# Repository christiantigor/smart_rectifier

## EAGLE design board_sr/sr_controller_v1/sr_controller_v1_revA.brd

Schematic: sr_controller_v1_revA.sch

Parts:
BAT1: BATTERY20PTH; BATTCOM_20MM_PTH
BUC_SPLY: AK300/2
C1, C9: C4.7uF; C0805
C3, C5, C14: C100N; C0805K
C4, C6: C1N; C0805K
C7, C8: C100uF; 153CLV-0605
C10, C12: C100nF; C0805
C11, C13: C22pF; C0805
D1: 1N4007; DO214AA
D3: TVSARRAY_5LANE; SOT363
DUMMY_A: AK500/2
DUMMY_B: AK500/2
DUMMY_C: AK500/2
F1, F5: 4A; FUSE1
F3: 10A; FUSE1
F4: 7A; FUSE1
FAN_A: 1X2-3.5MM
FAN_B: 1X2-3.5MM
FROM_LTC_REG: AK300/3
IC1: GSM_SIM900_LITERAL; SIM900_SMT
IC2: 74HC595D; SO16
INDICATOR_CONN: MA08-2
J1: SIMHOLDERSIM; SIMHOLDER
J2, J3, J4, J5, J6, J7, J8, J9: WIRE_HOLE-14AWG
K1: G5L; G5LE
LED1, LED2: LEDCHIPLED_0805; CHIPLED_0805
MDM_REG_A: AK300/2
MDM_REG_B: AK300/2
MDM_SPLY_HT_X1_X3: AK300/5
MDM_SPLY_HX_A: AK500/2
MDM_SPLY_HX_B: AK500/2
PCB1: RASPBERRY_PI_B+_NO_MOUNT; RASPBERRY_PI_B+
Q1: 32kHz; TC38H
R1, R2, R4, R7, R10, R12, R14, R15, R16, R22, R25, R28, R37, R38, R39, R40, R41, R42, R43, R44, R45, R46, R47, R48, R49, R50, R51: R10K; R0805
R3, R31, R34: R2K; R0805
R5, R6, R11, R13, R21, R24, R30, R35, R36: R1K; R0805
R8, R23, R26: R220R; R0805
R17, R29: R5.1K; R0805
R18, R19, R20: R22R; R0805
R27: R120R; R0805
R32: R270K; 0309/10
R33: R5.1K; 0309/10
SCADA_REG_A: AK300/2
SCADA_REG_B: AK300/2
SCADA_SPLY: AK500/2
SCPC_SPLY: AK300/2
SJ1, SJ2: SOLDERJUMPER; SOLDERJUMPER_ARROW_NOPASTE
SJ3: SOLDERJUMPERCLOSED; SOLDERJUMPER_CLOSEDWIRE
T1, T2, T3, T4: MMBT2222ALT1-NPN-SOT23-BEC; SOT23-BEC
TO_LTC_REG: AK300/2
U1: RTC_DS1307; SOIC8_150MIL
U3: RHT03_DHT-22_AM2302; RHT03_DHT-22
U$1: ARDUINO_PRO_MINI
U$2, U$4: ACS712; SO08
U$3, U$6: DCDCMODULE
U$5: FB0603; L0603
U$8: 74HC4053D; SO16
U$9: TRANSFORMER; TV16
VAC: AK300/2
V_ACCU: AK300/2
V_PWR_SPLY: AK300/2
X1: SMACONNECTOR; SMA90_DIP

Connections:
+3V3: R23.1, R26.1, R37.1, R38.1, R44.1, SJ2.2, U$5.2
+5V: C1.2, C3.2, C5.2, IC2.16 (VCC), INDICATOR_CONN.15, PCB1.2 (5V0), PCB1.4 (5V0), R1.1, R39.1, R40.1, R41.1, R42.1, R43.1, R45.1, R46.1, R47.1, R48.1, R49.1, R50.1, R51.1, SJ1.2, U1.8 (VCC), U3.VDD, U$1.21 (VCC), U$2.8 (VCC), U$4.8 (VCC), U$8.16 (VCC)
+6.5V: FROM_LTC_REG.3, MDM_SPLY_HX_A.1, R14.1
+13.5V: FROM_LTC_REG.1, MDM_SPLY_HT_X1_X3.4, R28.1
+19.5V: FROM_LTC_REG.2, MDM_SPLY_HX_A.2, R2.1
AGND: C3.1, C4.1, C5.1, C6.1, C14.1, SJ3.2, U$2.5 (GND), U$4.5 (GND)
ARDU_FLASH: INDICATOR_CONN.4, R45.2, U$1.14 (*11)
ARDU_RX: PCB1.26 (!CE!/GPIO7), U$1.2 (RXI)
ARDU_TX: PCB1.24 (!CE0!/GPIO8), R30.2, R31.1
CTRL_CHARGING: PCB1.40 (GPIO21), R6.1
CTRL_LED0: IC2.15 (QA), INDICATOR_CONN.13, R43.2
CTRL_LED1: IC2.1 (QB), INDICATOR_CONN.14, R51.2
CTRL_LED2: IC2.2 (QC), INDICATOR_CONN.11, R42.2
CTRL_LED3: IC2.3 (QD), INDICATOR_CONN.12, R50.2
CTRL_LED4: IC2.4 (QE), INDICATOR_CONN.9, R41.2
CTRL_LED5: IC2.5 (QF), INDICATOR_CONN.10, R49.2
CTRL_LED6: IC2.6 (QG), INDICATOR_CONN.7, R40.2
CTRL_LED7: IC2.7 (QH), INDICATOR_CONN.8, R48.2
CTRL_LED8: INDICATOR_CONN.5, R39.2, U$1.15 (12)
CTRL_LED9: INDICATOR_CONN.6, R46.2, U$1.16 (13)
CTRL_SIM_PWRKEY: PCB1.12 (GPIO18), R27.1
DHT_DATA: R1.2, U3.DATA, U$1.13 (*10)
GND: BAT1.2 (-), BUC_SPLY.2, C1.1, C7.-, C8.-, C9.1, C10.1, C11.1, C12.1, C13.1, D3.2 (A), FAN_A.1, FAN_B.1, IC1.P$17 (GND), IC1.P$18 (GND), IC1.P$29 (GND), IC1.P$39 (GND), IC1.P$45 (GND), IC1.P$46 (GND), IC1.P$53 (GND), IC1.P$54 (GND), IC1.P$58 (GND), IC1.P$59 (GND), IC1.P$61 (GND), IC1.P$62 (GND), IC1.P$63 (GND), IC1.P$64 (GND), IC1.P$65 (GND), IC2.8 (GND), IC2.13 (G), INDICATOR_CONN.16, J1.C5 (GND), MDM_REG_A.2, MDM_REG_B.1, MDM_SPLY_HT_X1_X3.2, MDM_SPLY_HX_B.1, PCB1.9 (GND), PCB1.25 (GND), PCB1.39 (GND), R3.2, R8.2, R11.2, R13.2, R15.2, R17.2, R22.1, R25.1, R29.2, R31.2, R34.2, SCADA_REG_A.2, SCADA_REG_B.1, SCADA_SPLY.2, SCPC_SPLY.2, SJ3.1, T1.E, T2.E, T3.E, T4.E, TO_LTC_REG.2, U1.4 (GND), U3.GND, U$1.4 (GND), U$1.23 (GND), U$3.GND#0 (GNDI), U$3.GND#1 (GNDO), U$6.GND#0 (GNDI), U$6.GND#1 (GNDO), U$8.6 (/E), U$8.7 (VEE), U$8.8 (GND), V_ACCU.1, V_PWR_SPLY.1, X1.GND1, X1.GND2, X1.GND3, X1.GND4
GPIO11: IC1.P$67 (GPIO11)
GPIO12: IC1.P$68 (GPIO12)
MDM_INDC_0: MDM_SPLY_HX_B.2, PCB1.38 (GPIO20), R5.2
MDM_INDC_1: MDM_SPLY_HT_X1_X3.1, PCB1.32 (GPIO12), R35.2
MDM_INDC_2: MDM_SPLY_HT_X1_X3.3, PCB1.36 (GPIO16), R36.2
unnamed: R32.1, VAC.2
unnamed: U$9.IB, VAC.1
unnamed: Q1.1, U1.1 (X1)
unnamed: Q1.2, U1.2 (X2)
unnamed: BAT1.1 (+), U1.3 (VBAT)
unnamed: U$8.13 (1Y1), U$8.15 (2Z)
unnamed: U$8.4 (3Z), U$8.12 (1Y0)
unnamed: SJ1.1, U$3.VOUT
unnamed: SJ2.1, U$6.VOUT
unnamed: C4.2, U$2.6 (FILT)
unnamed: R6.2, T4.B
unnamed: C6.2, U$4.6 (FILT)
unnamed: F1.1A, MDM_REG_B.2
unnamed: F3.1A, SCADA_REG_B.2
unnamed: IC1.P$60 (RF_ANT), X1.ANTENNA (ANT)
unnamed: C7.+, C8.+, IC1.P$55 (VBAT1), IC1.P$56 (VBAT2), IC1.P$57 (VBAT3), U$5.1
unnamed: C9.2, IC1.P$26 (VRTC)
unnamed: IC1.P$33 (SIM_RST), R18.1
unnamed: IC1.P$32 (SIM_CLK), R19.1
unnamed: IC1.P$31 (SIM_DATA), R20.1
unnamed: LED1.C, T1.C
unnamed: LED1.A, R23.2
unnamed: LED2.C, T2.C
unnamed: R21.2, R22.2, T1.B
unnamed: LED2.A, R26.2
unnamed: R24.2, R25.2, T2.B
unnamed: R27.2, T3.B
unnamed: D1.A, K1.2, T4.C
unnamed: R30.1, U$1.1 (TXO)
unnamed: R32.2, U$9.IA
unnamed: C14.2, R33.1, U$9.OB
RPI_3V3: PCB1.17 (3V3), R5.1, R35.1, R36.1
RPI_FLASH: INDICATOR_CONN.3, PCB1.16 (GEN4/GPIO23), R38.2
RTC_SCL: PCB1.5 (GPIO3/SCL1), U1.6 (SCL)
RTC_SDA: PCB1.3 (GPIO2/SDA1), U1.5 (SDA)
SEL_SENSOR_1: U$1.12 (*9), U$8.11 (S1)
SEL_SENSOR_2: U$1.11 (8), U$8.10 (S2)
SEL_SENSOR_3: U$1.10 (7), U$8.9 (S3)
SENSOR_BUC: R12.2, R13.1, U$1.25 (A4)
SENSOR_IBAT: U$1.18 (A1), U$4.7 (VOUT)
SENSOR_ILOAD: U$1.20 (A3), U$2.7 (VOUT)
SENSOR_MDM: U$1.27 (A6), U$8.14 (1Z)
SENSOR_MDM_0: R14.2, R15.1, U$8.5 (3Y0)
SENSOR_MDM_1: R28.2, R29.1, U$8.2 (2Y0)
SENSOR_MDM_2: R2.2, R3.1, U$8.3 (3Y1)
SENSOR_MDM_3: R4.2, R34.1, U$8.1 (2Y1)
SENSOR_SCADA: R16.2, R17.1, U$1.26 (A5)
SENSOR_SCPC: R10.2, R11.1, U$1.28 (A7)
SENSOR_VAC: R33.2, U$1.17 (A0), U$9.OA
SENSOR_VBAT: R7.2, R8.1, U$1.19 (A2)
SIM_NETLIGHT: IC1.P$52 (NETLIGHT), INDICATOR_CONN.1, R24.1, R37.2
SIM_PWRKEY: IC1.P$1 (PWRKEY), T3.C
SIM_RX: IC1.P$10 (RXD), PCB1.8 (TXD0/GPIO14)
SIM_STATUS: IC1.P$66 (STATUS), INDICATOR_CONN.2, R21.1, R44.2
SIM_TX: IC1.P$9 (TXD), PCB1.10 (RXD0/GPIO15)
SR_DS: IC2.14 (SER), U$1.8 (*5)
SR_RST: IC2.10 (SCL), R47.2, U$1.5 (2)
SR_SHCP: IC2.11 (SCK), U$1.6 (*3)
SR_STCP: IC2.12 (RCK), U$1.7 (4)
USIM_CLK: D3.4 (C3), J1.C3 (CLK), R19.2
USIM_DATA: D3.1 (C1), J1.C7 (I/O), R20.2
USIM_RST: D3.3 (C2), J1.C2 (RST), R18.2
USIM_VDD: C10.2, C11.2, C12.2, C13.2, D3.5 (C4), IC1.P$30 (SIM_VDD), J1.C1 (VCC)
VBAT: J4.P$1, J5.P$1, R7.1, U$4.3 (IP-), U$4.4 (IP-), V_ACCU.2
VBUC: BUC_SPLY.1, F4.1A, J8.P$1, J9.P$1, R12.1
VLOAD: F1.2A, F3.2A, F4.2A, F5.2A, J2.P$1, J3.P$1, U$2.3 (IP-), U$2.4 (IP-)
VMDM: MDM_REG_A.1, MDM_SPLY_HT_X1_X3.5, R4.1, TO_LTC_REG.1, U$3.VIN, U$6.VIN
VPWR_SPLY: K1.P, V_PWR_SPLY.2
VSCADA: D1.C, FAN_A.2, FAN_B.2, K1.1, R16.1, SCADA_REG_A.1, SCADA_SPLY.1
VSCPC: F5.1A, J6.P$1, J7.P$1, R10.1, SCPC_SPLY.1
VSPLY: K1.S, U$2.1 (IP+), U$2.2 (IP+), U$4.1 (IP+), U$4.2 (IP+)

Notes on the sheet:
Drawn by:
Checked by:
FLYFISH TECHNOLOGIES d.o.o.
Ivan Zilic
v0.1

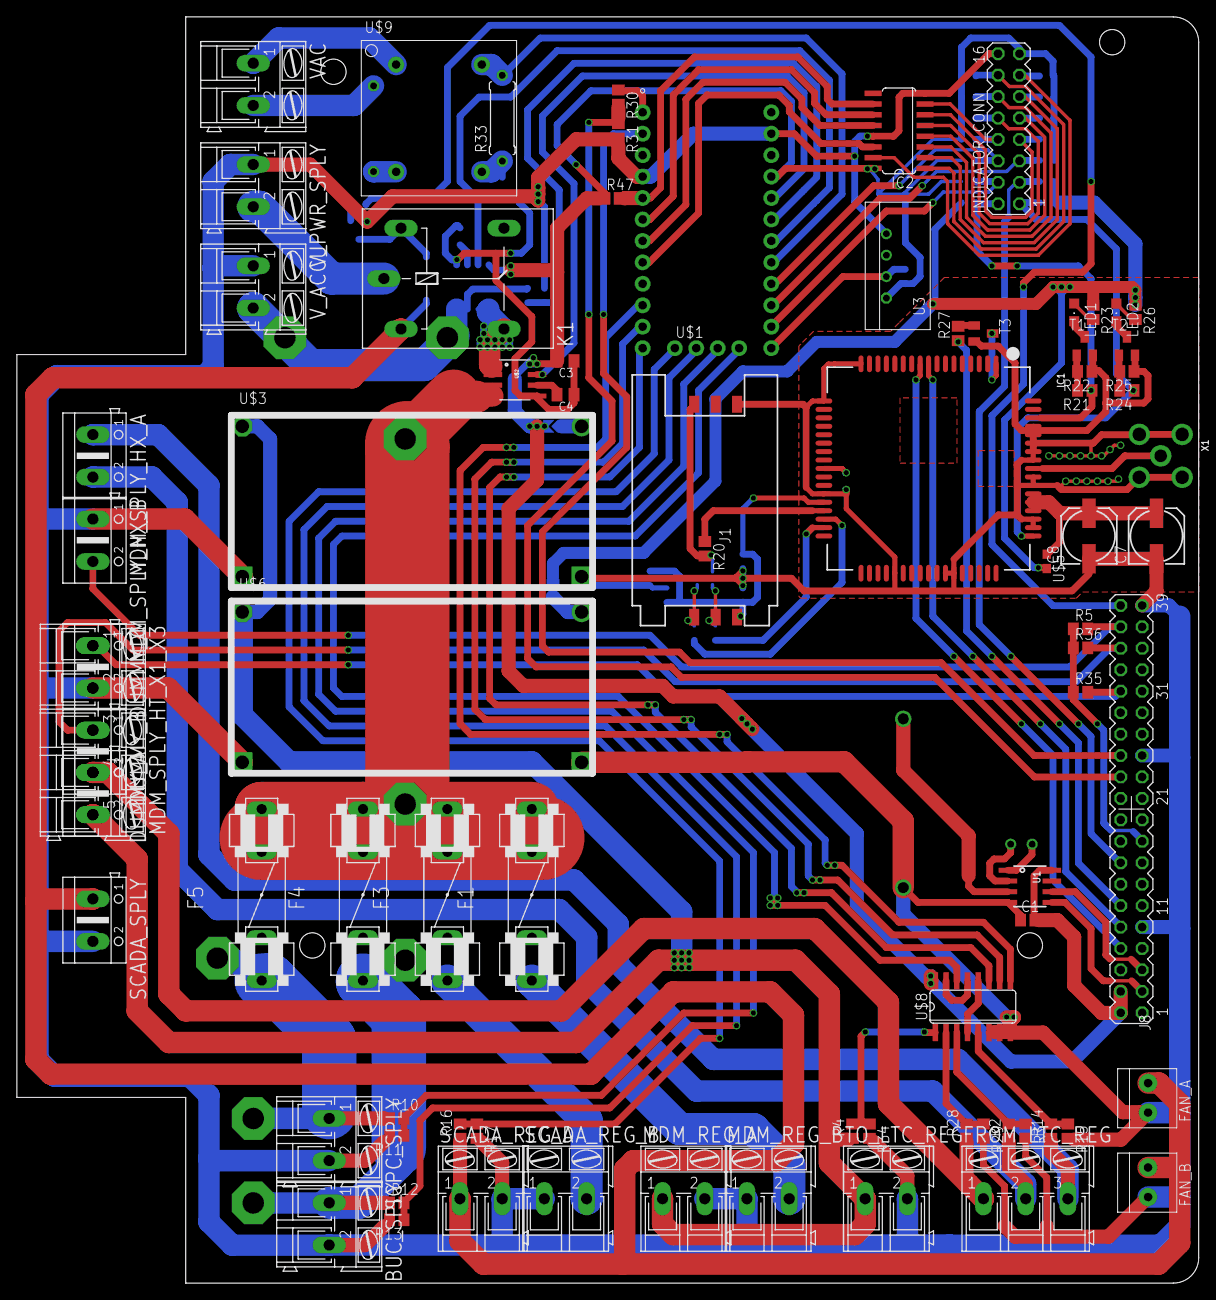
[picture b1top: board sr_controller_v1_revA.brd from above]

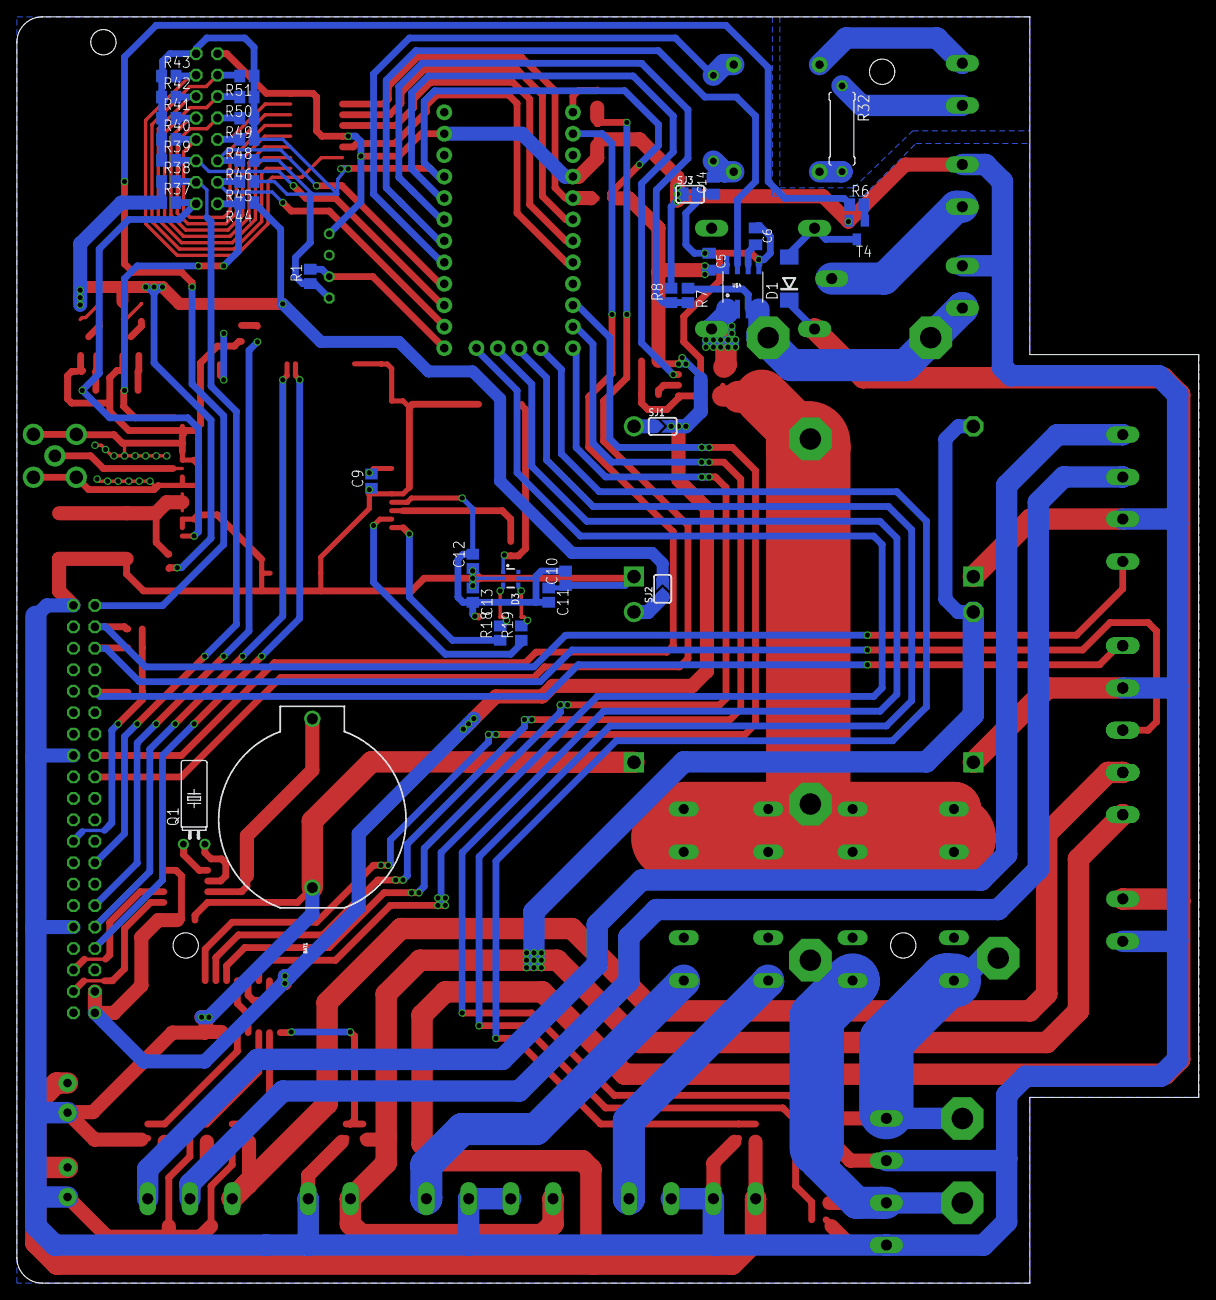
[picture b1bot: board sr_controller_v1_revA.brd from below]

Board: 2 copper layers, 140.0 x 150.0 mm, 125 parts (38 on the bottom side), 97 nets.

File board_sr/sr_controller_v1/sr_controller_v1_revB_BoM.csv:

"Qty";"Value";"Device";"Package";"Parts";"Description";"";
"10";"";"AK300/2";"AK300/2";"BUC_SPLY, MDM_REG_A, MDM_REG_B, SCADA_REG_A, SCADA_REG_B, SCPC_SPLY, TO_LTC_REG, VAC, V_ACCU, V_PWR_SPLY";"CONNECTOR";"";
"1";"";"AK300/3";"AK300/3";"FROM_LTC_REG";"CONNECTOR";"";
"1";"";"AK300/5";"AK300/5";"MDM_SPLY_HT_X1_X3";"CONNECTOR";"";
"3";"";"AK500/2";"AK500/2";"MDM_SPLY_HX_A, MDM_SPLY_HX_B, SCADA_SPLY";"CONNECTOR";"";
"1";"";"BATTERY20PTH";"BATTCOM_20MM_PTH";"BAT1";"Battery Holders";"";
"1";"";"GSM_SIM900_LITERAL";"SIM900_SMT";"IC1";"SIM900 Quad-Band GSM/GPRS Module";"";
"2";"";"LEDCHIPLED_0805";"CHIPLED_0805";"LED1, LED2";"LED";"";
"1";"";"MA08-2";"MA08-2";"INDICATOR_CONN";"PIN HEADER";"";
"4";"";"MMBT2222ALT1-NPN-SOT23-BEC";"SOT23-BEC";"T1, T2, T3, T4";"NPN Transistror";"";
"1";"";"RHT03_DHT-22_AM2302";"RHT03_DHT-22";"U3";"RHT03 / DHT-22 / AM2302";"";
"1";"";"RTC_DS1307";"SOIC8_150MIL";"U1";"DS1307 I2C RTC with 56-Bytes RAM";"";
"1";"";"SIMHOLDERSIM";"SIMHOLDER";"J1";"SIM Socket";"";
"1";"";"SMACONNECTOR";"SMA90_DIP";"X1";"SMA Connector";"";
"2";"";"SOLDERJUMPER";"SOLDERJUMPER_ARROW_NOPASTE";"SJ1, SJ2";"SMD Solder JUMPER";"";
"1";"";"SOLDERJUMPERCLOSED";"SOLDERJUMPER_CLOSEDWIRE";"SJ3";"SMD Solder JUMPER";"";
"1";"";"TAC_SWITCHPTH";"TACTILE-PTH";"RPI_RESET";"Momentary Switch";"";
"1";"";"TVSARRAY_5LANE";"SOT363";"D3";"Voltage Transient Suppressor Array";"";
"1";"10A";"FUSE2P";"FUSE1";"F3";"FUSE";"";
"1";"1N4007";"DIODE-DO214AA";"DO214AA";"D1";"DIODE";"";
"2";"1X2-3.5MM";"1X2-3.5MM";"1X2-3.5MM";"FAN_A, FAN_B";"3.5mm Terminal block";"";
"1";"32kHz";"CRYSTALTC38H";"TC38H";"Q1";"CRYSTAL";"";
"2";"4A";"FUSE2P";"FUSE1";"F1, F5";"FUSE";"";
"1";"74HC4053D";"74HC4053D";"SO16";"U$8";"";"";
"1";"74HC595D";"74HC595D";"SO16";"IC2";"8-bit SHIFT REGISTER, output latch";"";
"1";"7A";"FUSE2P";"FUSE1";"F4";"FUSE";"";
"2";"ACS712";"ACS712";"SO08";"U$2, U$4";"Hall-effect-based isolated linear current sensor";"";
"1";"ARDUINO_PRO_MINI";"ARDUINO_PRO_MINI";"ARDUINO_PRO_MINI";"U$1";"";"";
"3";"C100N";"C-EUC0805K";"C0805K";"C2, C3, C5";"CAPACITOR, European symbol";"";
"2";"C100nF";"C-EUC0805";"C0805";"C10, C12";"CAPACITOR, European symbol";"";
"2";"C100uF";"CPOL-EU153CLV-0605";"153CLV-0605";"C7, C8";"POLARIZED CAPACITOR, European symbol";"";
"2";"C1N";"C-EUC0805K";"C0805K";"C4, C6";"CAPACITOR, European symbol";"";
"2";"C22pF";"C-EUC0805";"C0805";"C11, C13";"CAPACITOR, European symbol";"";
"2";"C4.7uF";"C-EUC0805";"C0805";"C1, C9";"CAPACITOR, European symbol";"";
"2";"DCDCMODULE";"DCDCMODULE";"DCDCMODULE";"U$3, U$6";"";"";
"1";"FB0603";"L0603";"L0603";"L1";"";"";
"1";"G5L";"G5L";"G5LE";"K1";"RELAY";"";
"27";"R10K";"R-EU_R0805";"R0805";"R1, R2, R4, R7, R10, R12, R14, R15, R16, R22, R25, R28, R37, R38, R39, R40, R41, R42, R43, R44, R45, R46, R47, R48, R49, R50, R51";"RESISTOR, European symbol";"";
"1";"R120R";"R-EU_R0805";"R0805";"R27";"RESISTOR, European symbol";"";
"10";"R1K";"R-EU_R0805";"R0805";"R5, R6, R11, R13, R21, R24, R30, R35, R36, R53";"RESISTOR, European symbol";"";
"1";"R2.2K";"R-EU_0309/10";"0309/10";"R33";"RESISTOR, European symbol";"";
"3";"R220R";"R-EU_R0805";"R0805";"R8, R23, R26";"RESISTOR, European symbol";"";
"3";"R22R";"R-EU_R0805";"R0805";"R18, R19, R20";"RESISTOR, European symbol";"";
"1";"R270K";"R-EU_0309/10";"0309/10";"R32";"RESISTOR, European symbol";"";
"3";"R2K";"R-EU_R0805";"R0805";"R3, R31, R34";"RESISTOR, European symbol";"";
"2";"R470K";"R-EU_R0805";"R0805";"R9, R52";"RESISTOR, European symbol";"";
"2";"R5.1K";"R-EU_R0805";"R0805";"R17, R29";"RESISTOR, European symbol";"";
"1";"RASPBERRY_PI_B+_NO_MOUNT";"RASPBERRY_PI_B+_NO_MOUNT";"RASPBERRY_PI_B+";"PCB1";"Raspberry Pi B+";"";
"1";"TRANSFORMER";"TRANSFORMER";"TV16";"TV16";"";"";
"8";"WIRE_HOLE-14AWG";"WIRE_HOLE-14AWG";"WIRE_HOLE-14AWG";"J2, J3, J4, J5, J6, J7, J8, J9";"Solder point for 14AWG wire";"";

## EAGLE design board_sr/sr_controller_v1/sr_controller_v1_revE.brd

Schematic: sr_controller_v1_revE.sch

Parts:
ADJ_VPWRSPLY: AK300/2
B1: RB1A
BAT1: BATTERY20PTH; BATTCOM_20MM_PTH
C1: C4.7uF; C0805
C2: C470uF; E3,5-8
C3, C5: C100nF; C0805K
C4, C6: C1nF; C0805K
D1, D2: 1N4004; DO41-10
D3: 1N4728; DO41Z10
F1, F2, F3: 5A; BLADE_FUSE_HOLDER
FAN: HEADER_1X02
FROM_GREY_REG: AK300/2
FROM_LTC_REG_A: AK300/2
FROM_LTC_REG_B: AK300/2
IC3: LM741D; SO08
INDICATOR_CONN: MA03-2
LED1: LEDCHIP-LED0805; CHIP-LED0805
OUT_+6V5, OUT_+12V, OUT_+13V5, OUT_+19V5, OUT_+24V, OUT_+48V_A, OUT_+48V_B: MKDSN1,5/2-5,08
PCB1: RASPBERRY_PI_B+_NO_MOUNT; RASPBERRY_PI_B+
Q1: 32kHz; TC38H
Q2: BD140; TO126AV
R1, R2, R4, R7, R9, R10, R12, R14, R15, R16, R24, R25, R26, R27, R28, R54: R10K; R0805
R3, R31, R34: R2K; R0805
R5: R150K; R0805
R6: R100K; R0805
R8, R18: R220R; R0805
R11, R13, R20, R21, R30, R53: R1K; R0805
R17, R22, R29: R5.1K; R0805
R32: R270K; 0309/10
R33: R5.1K; 0309/10
R55: R10K; P642
R57: R47R; R0805
RPI_RESET: TAC_SWITCHPTH; TACTILE-PTH
SJ1, SJ2: SOLDERJUMPER; SOLDERJUMPER_ARROW_NOPASTE
SJ3: SOLDERJUMPERCLOSED; SOLDERJUMPER_CLOSEDWIRE
SJ6: SOLDERJUMPERREFLOW; SOLDERJUMPER_REFLOW
T1: MMBT2222ALT1-NPN-SOT23-BEC; SOT23-BEC
TO_GREY_REG: AK300/2
TO_LTC_REG: AK300/2
TV16: TRANSFORMER; TV16
U1: RTC_DS1307; SOIC8_150MIL
U3: RHT03_DHT-22_AM2302; RHT03_DHT-22
U$1: ARDUINO_PRO_MINI
U$2, U$4: ACS712; SO08
U$3, U$6: DCDCMODULE
U$7, U$8: 74HC4053D; SO16
VAC: AK300/2
VPWRSPLY&VBAT: AK300/3

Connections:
+3V3: INDICATOR_CONN.5, LED1.A, R24.1, R25.1, R26.1, R27.1, SJ2.2
+5V: C1.2, C3.2, C5.2, PCB1.2 (5V0), PCB1.4 (5V0), R1.1, R21.2, SJ1.2, U1.8 (VCC), U3.VDD, U$1.21 (VCC), U$2.8 (VCC), U$4.8 (VCC), U$7.16 (VCC), U$8.16 (VCC)
+6V5: FROM_LTC_REG_B.2, OUT_+6V5.2, R14.1
+12V: D2.C, FAN.1, FROM_LTC_REG_B.1, IC3.7 (V+), OUT_+12V.2, R5.1, R16.1, R54.1
+13V5: FROM_LTC_REG_A.2, OUT_+13V5.2, R28.1
+19V5: FROM_LTC_REG_A.1, OUT_+19V5.2, R2.1
+24V: FROM_GREY_REG.1, OUT_+24V.2, R4.1, TO_LTC_REG.1, U$3.VIN, U$6.VIN
+48V_A: F2.1, OUT_+48V_A.2, R10.1
+48V_B: F3.1, OUT_+48V_B.2, R12.1
ADJ_VOLTAGE: ADJ_VPWRSPLY.2, R22.2
AGND: C3.1, C4.1, C5.1, C6.1, D3.A, SJ3.2, SJ6.1, U$2.5 (GND), U$4.5 (GND)
ARDU_RX: PCB1.8 (TXD0/GPIO14), U$1.2 (RXI)
ARDU_TX: PCB1.10 (RXD0/GPIO15), R30.2, R31.1
CTRL_CHARGING: PCB1.12 (GPIO18), R20.1
DHT_DATA: R1.2, U3.DATA, U$1.13 (*10)
GND: ADJ_VPWRSPLY.1, BAT1.2 (-), C1.1, FROM_GREY_REG.2, IC3.4 (V-), INDICATOR_CONN.6, OUT_+6V5.1, OUT_+12V.1, OUT_+13V5.1, OUT_+19V5.1, OUT_+24V.1, OUT_+48V_A.1, OUT_+48V_B.1, PCB1.9 (GND), PCB1.25 (GND), PCB1.39 (GND), Q2.C, R3.2, R6.2, R8.2, R11.2, R13.2, R15.2, R17.2, R18.2, R29.2, R31.2, R34.2, R55.1, RPI_RESET.3, RPI_RESET.4, SJ3.1, T1.E, TO_GREY_REG.1, TO_LTC_REG.2, U1.4 (GND), U3.GND, U$1.4 (GND), U$1.23 (GND), U$3.GND#0 (GNDI), U$3.GND#1 (GNDO), U$6.GND#0 (GNDI), U$6.GND#1 (GNDO), U$7.6 (/E), U$7.7 (VEE), U$7.8 (GND), U$8.6 (/E), U$8.7 (VEE), U$8.8 (GND), VPWRSPLY&VBAT.1
INDC_HEALTH_BLUE: INDICATOR_CONN.3, PCB1.35 (GPIO19), R26.2
INDC_HEALTH_GREEN: INDICATOR_CONN.2, PCB1.38 (GPIO20), R25.2
INDC_HEALTH_RED: INDICATOR_CONN.1, PCB1.37 (GPIO26), R24.2
INDC_SPLY_OUTS: INDICATOR_CONN.4, PCB1.36 (GPIO16), R27.2
unnamed: R32.1, VAC.2
unnamed: TV16.IB, VAC.1
unnamed: Q1.2, U1.1 (X1)
unnamed: Q1.1, U1.2 (X2)
unnamed: BAT1.1 (+), U1.3 (VBAT)
unnamed: U$8.13 (1Y1), U$8.15 (2Z)
unnamed: U$8.4 (3Z), U$8.12 (1Y0)
unnamed: SJ1.1, U$3.VOUT
unnamed: SJ2.1, U$6.VOUT
unnamed: C4.2, U$2.6 (FILT)
unnamed: U$7.13 (1Y1), U$7.15 (2Z)
unnamed: LED1.C, R53.1
unnamed: IC3.3 (+IN), R54.2, R55.2
unnamed: C6.2, U$4.6 (FILT)
unnamed: F1.1, TO_GREY_REG.2
unnamed: IC3.2 (-IN), R5.2, R6.1
unnamed: D1.A, R21.1, T1.C
unnamed: D2.A, FAN.2, Q2.E
unnamed: B1.AC1, R33.2, TV16.OA
unnamed: R20.2, T1.B
unnamed: D1.C, R22.1
unnamed: B1.-, C2.-, SJ6.2
unnamed: U$7.4 (3Z), U$7.12 (1Y0)
unnamed: R30.1, U$1.1 (TXO)
unnamed: R32.2, TV16.IA
unnamed: B1.AC2, R33.1, TV16.OB
unnamed: IC3.6 (OUT), R57.2
unnamed: Q2.B, R57.1
RPI_RESET: PCB1.32 (GPIO12), R53.2, RPI_RESET.1, RPI_RESET.2
RTC_SCL: PCB1.5 (GPIO3/SCL1), U1.6 (SCL)
RTC_SDA: PCB1.3 (GPIO2/SDA1), U1.5 (SDA)
SEL_SENSOR_1: U$1.14 (*11), U$7.11 (S1), U$8.11 (S1)
SEL_SENSOR_2: U$1.15 (12), U$7.9 (S3), U$7.10 (S2), U$8.9 (S3), U$8.10 (S2)
SENSOR_+6V5: R14.2, R15.1, U$8.5 (3Y0)
SENSOR_+12V: R16.2, R17.1, U$8.3 (3Y1)
SENSOR_+13V5: R28.2, R29.1, U$8.2 (2Y0)
SENSOR_+19V5: R2.2, R3.1, U$8.1 (2Y1)
SENSOR_+24V: R4.2, R34.1, U$7.5 (3Y0)
SENSOR_+48V_A: R10.2, R11.1, U$7.2 (2Y0)
SENSOR_+48V_B: R12.2, R13.1, U$7.3 (3Y1)
SENSOR_IBAT: U$1.18 (A1), U$4.7 (VOUT)
SENSOR_ILOAD: U$1.17 (A0), U$2.7 (VOUT)
SENSOR_SPLY_A: U$1.28 (A7), U$7.14 (1Z)
SENSOR_SPLY_B: U$1.27 (A6), U$8.14 (1Z)
SENSOR_VAC: B1.+, C2.+, D3.C, U$1.20 (A3)
SENSOR_VBAT: R7.2, R8.1, U$7.1 (2Y1)
SENSOR_VPWRSPLY: R9.2, R18.1, U$1.19 (A2)
VBAT: R7.1, U$4.3 (IP-), U$4.4 (IP-), VPWRSPLY&VBAT.3
VLOAD: F1.2, F2.2, F3.2, U$2.3 (IP-), U$2.4 (IP-)
VPWRSPLY: R9.1, U$2.1 (IP+), U$2.2 (IP+), U$4.1 (IP+), U$4.2 (IP+), VPWRSPLY&VBAT.2

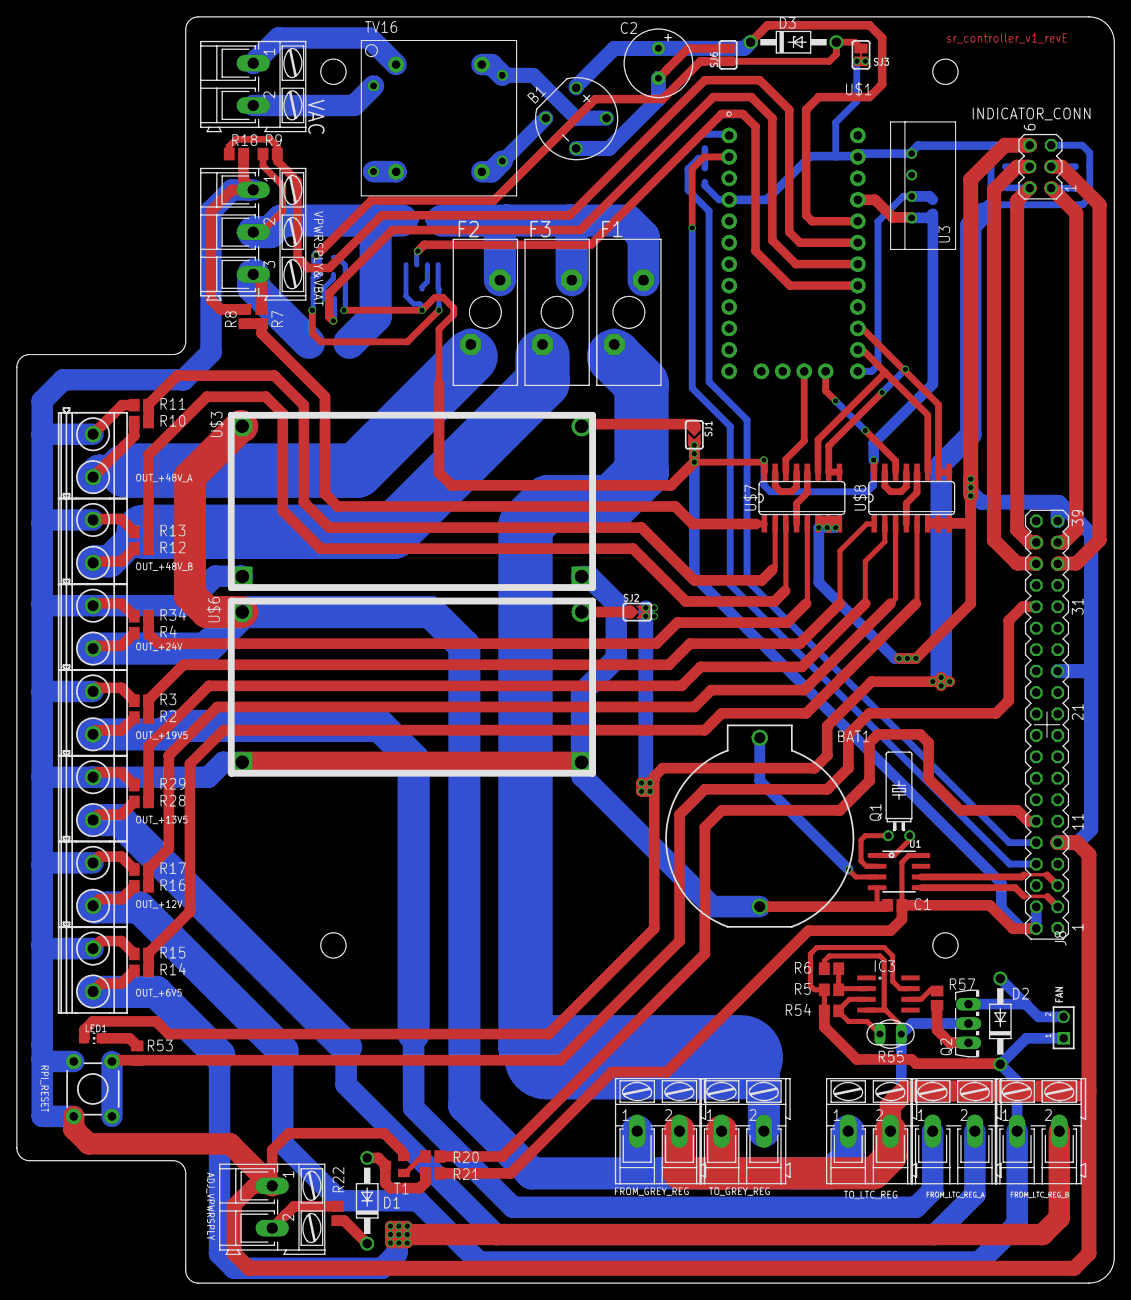
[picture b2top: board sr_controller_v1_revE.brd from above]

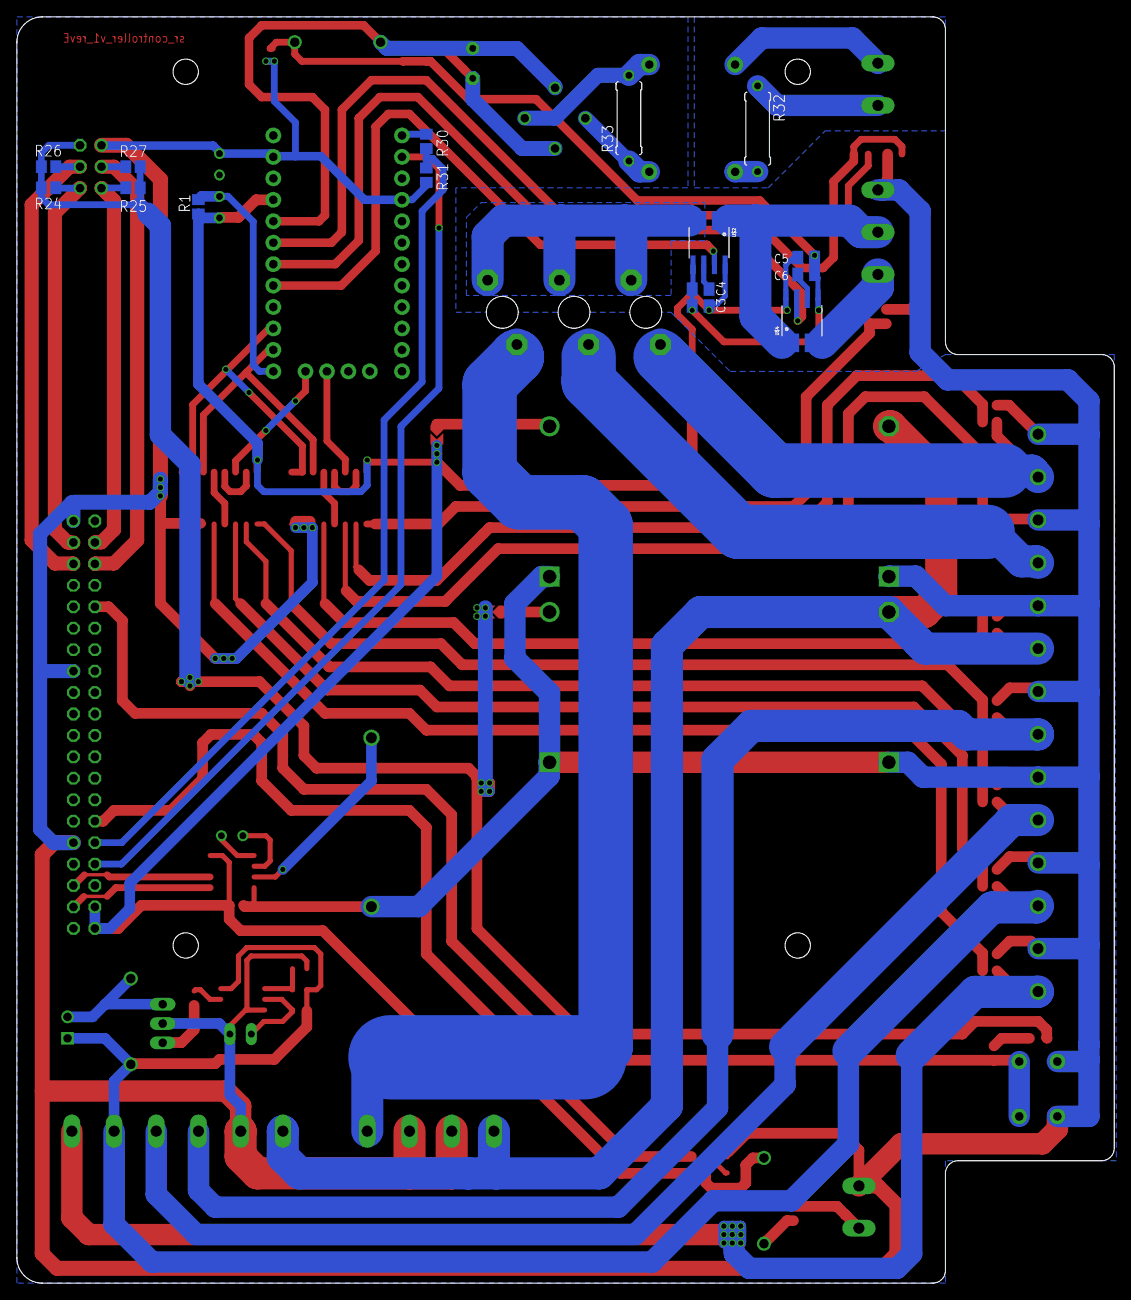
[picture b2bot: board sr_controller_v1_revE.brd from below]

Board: 2 copper layers, 130.0 x 150.0 mm, 88 parts (15 on the bottom side), 70 nets.

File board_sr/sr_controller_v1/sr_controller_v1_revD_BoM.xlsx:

Reference | Part Number | Description | Value | Amount | Link
ADJ_VPWRSPLY, FROM_GREY_REG, FROM_LTC_REG_A, FROM_LTC_REG_B, TO_GREY_REG, TO_LT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 | AK300/2 | 2 Pin Blue Connector |  | 7
VPWRSPLY&VBAT | AK300/3 | 3 Pin Blue Connector |  | 1
OUT_+6V5, OUT_+12V, OUT_+13V5, OUT_+19V5, OUT_+24V, OUT_+48V_A, OUT_+48V_B | AK500/2 | 2 Pin Green Connector |  | 7
BAT1 | BATTERY20PTH | Battery Holders |  | 1
FAN | HEADER_1X02 | 2-Pin 0,254cm / 0.1 Header" |  | 1
LED1 | LEDCHIP-LED0805 | LED |  | 1
INDICATOR_CONN | MA03-2 | Male Pin Header |  | 1
T1 | MMBT2222ALT1-NPN-SOT23-BEC | NPN Transistror 2222 |  | 1
B1 | RB1A | Diode Bridge Rectifier |  | 1
U3 | RHT03_DHT-11_AM2302 | DHT 11 Temperature and Humidity Sensor |  | 1
U1 | RTC_DS1307 | DS1307 RTC |  | 1
SJ1, SJ2 | SOLDERJUMPER | leave this unassembled |  | 2
SJ3 | SOLDERJUMPERCLOSED | leave this unassembled |  | 1
SJ6 | SOLDERJUMPERREFLOW | solder the jumper |  | 1
RPI_RESET | TAC_SWITCHPTH | Tactile Switch |  | 1
D1, D2 | 1N4004 | DIODE | 1N4004 | 2
D3 | 1N4728 | Z DIODE | 1N4728 | 1
Q1 | CRYSTALTC38H | CRYSTAL | 32kHz | 1
F1, F2, F3 | BLADE_FUSE_HOLDER | Fuse Holder and The Fuse | 5A | 3
U$7, U$8 | 74HC4053D | Analog Mux | 74HC4053D | 2
U$2, U$4 | ACS712 | Current Sensor | ACS712 | 2
U$1 | ARDUINO_PRO_MINI | Female Pin Header | ARDUINO_PRO_MINI | 1
Q2 | BD140 | PNP TRANSISTOR | BD140 | 1
C3, C5 | C-EUC0805K | C0805 | C100nF | 2
C4, C6 | C-EUC0805K | C0805 | C1nF | 2
C1 | C-EUC0805 | C0805 | C4.7uF | 1
C2 | CPOL-EUE3.5-8 | leave this unassembled | C470uF | 1
U$3, U$6 | DCDCMODULE | Voltage Regulator | DCDCMODULE | 2
IC3 | LM741D | OP AMP | LM741D | 1
R6 | R-EU_R0805 | R0805 | R100K | 1
R55 | NTC642-6 | NTC Thermistor | R10K | 1
R1, R2, R4, R7, R9, R10, R12, R14, R15, R16, R24, R25, R26, R27, R28, R54 | R-EU_R0805 | R0805 | R10K | 16
R5 | R-EU_R0805 | R0805 | R150K | 1
R11, R13, R20, R21, R30, R53 | R-EU_R0805 | R0805 | R1K | 6
R8, R18 | R-EU_R0805 | R0805 | R220R | 2
R32 | R-EU_0309/10 | RESISTOR, European symbol | R270K | 1
R3, R31, R34 | R-EU_R0805 | R0805 | R2K | 3
R57 | R-EU_R0805 | R0805 | R47R | 1
R33 | R-EU_0309/10 | RESISTOR, European symbol | R5.1K | 1
R17, R22, R29 | R-EU_R0805 | R0805 | R5.1K | 3
PCB1 | RASPBERRY_PI_B+_NO_MOUNT | Male Pin Header | RASPBERRY_PI_B+_NO_MOUNT | 1
TV16 | TRANSFORMER | YHDC TV16 2.5mm Transformer | TRANSFORMER | 1
Notes:
Add tin layer on unmasked area on bottom layer

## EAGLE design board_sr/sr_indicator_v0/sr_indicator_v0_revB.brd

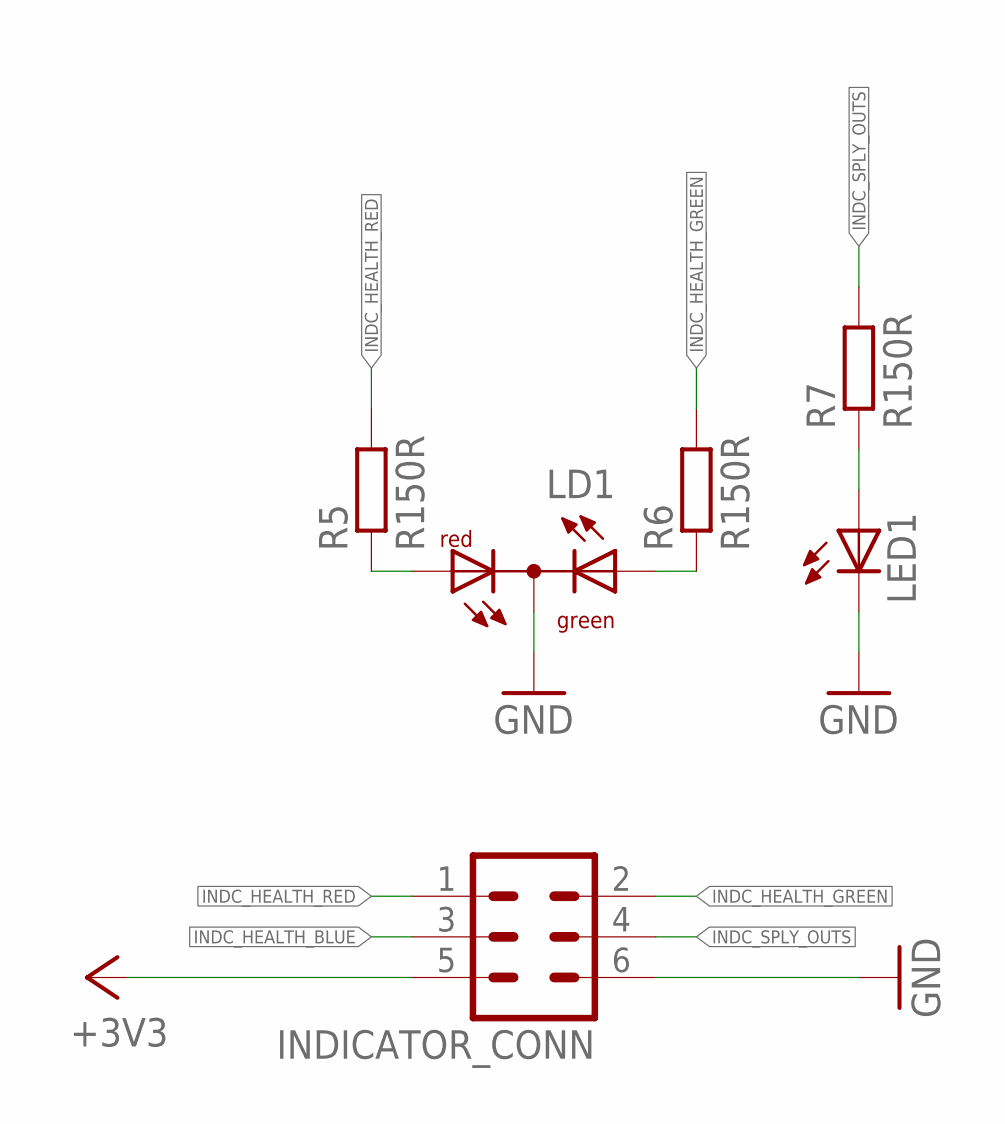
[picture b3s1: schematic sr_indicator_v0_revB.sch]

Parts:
INDICATOR_CONN: MA03-2
LD1: DUOLED-RG-C; DUOLED-C-5MM
LED1: LED5MM
R5, R6, R7: R150R; M0805

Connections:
+3V3: INDICATOR_CONN.5
GND: INDICATOR_CONN.6, LD1.C, LED1.K (C)
INDC_HEALTH_BLUE: INDICATOR_CONN.3
INDC_HEALTH_GREEN: INDICATOR_CONN.2, R6.2
INDC_HEALTH_RED: INDICATOR_CONN.1, R5.2
INDC_SPLY_OUTS: INDICATOR_CONN.4, R7.2
unnamed: LD1.AR, R5.1
unnamed: LD1.AX (AG), R6.1
unnamed: LED1.A, R7.1

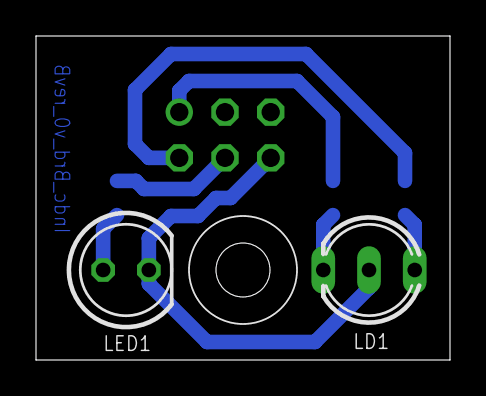
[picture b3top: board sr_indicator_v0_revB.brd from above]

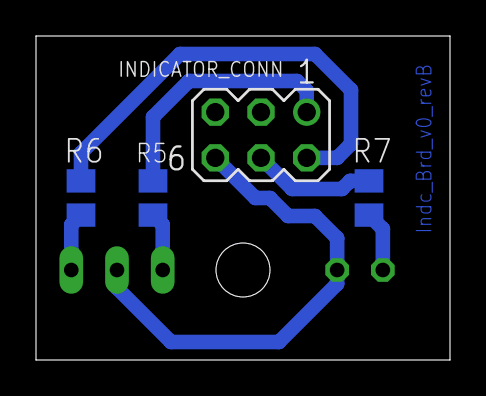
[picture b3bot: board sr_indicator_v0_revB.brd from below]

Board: 2 copper layers, 23.0 x 18.0 mm, 6 parts (4 on the bottom side), 7 nets.

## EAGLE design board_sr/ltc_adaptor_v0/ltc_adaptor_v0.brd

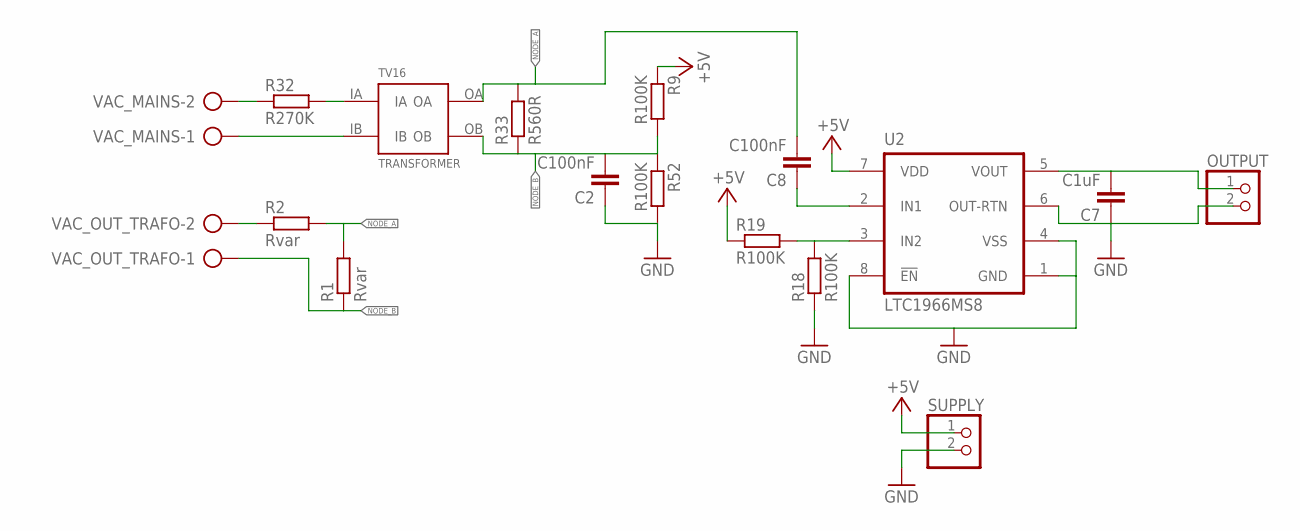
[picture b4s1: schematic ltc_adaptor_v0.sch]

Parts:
C2, C8: C100nF; C0805K
C7: C1uF; C0805K
OUTPUT: HEADER-1X2ROUND; 1X02_ROUND
R1, R2: Rvar; R0805
R9, R18, R19, R52: R100K; R0805
R32: R270K; 0309/10
R33: R560R; 0309/10
SUPPLY: HEADER-1X2ROUND; 1X02_ROUND
TV16: TRANSFORMER; TV16
U2: LTC1966MS8; MSOP08
VAC_MAINS: AK300/2
VAC_OUT_TRAFO: AK300/2

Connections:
+5V: R9.1, R19.1, SUPPLY.1, U2.7 (VDD)
GND: C2.1, C7.1, OUTPUT.2, R18.1, R52.2, SUPPLY.2, U2.1 (GND), U2.4 (VSS), U2.6 (OUT-RTN), U2.8 (!EN!)
unnamed: R32.1, VAC_MAINS.2
unnamed: TV16.IB, VAC_MAINS.1
unnamed: R2.1, VAC_OUT_TRAFO.2
unnamed: C7.2, OUTPUT.1, U2.5 (VOUT)
unnamed: R18.2, R19.2, U2.3 (IN2)
unnamed: C8.1, U2.2 (IN1)
unnamed: R32.2, TV16.IA
NODE_A: C8.2, R1.2, R2.2, R33.2, TV16.OA
NODE_B: C2.2, R1.1, R9.2, R33.1, R52.1, TV16.OB, VAC_OUT_TRAFO.1

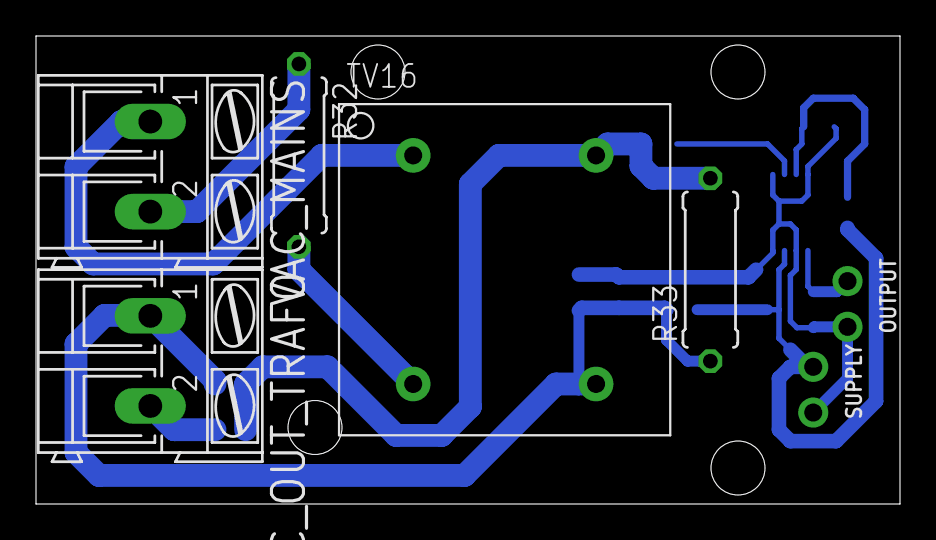
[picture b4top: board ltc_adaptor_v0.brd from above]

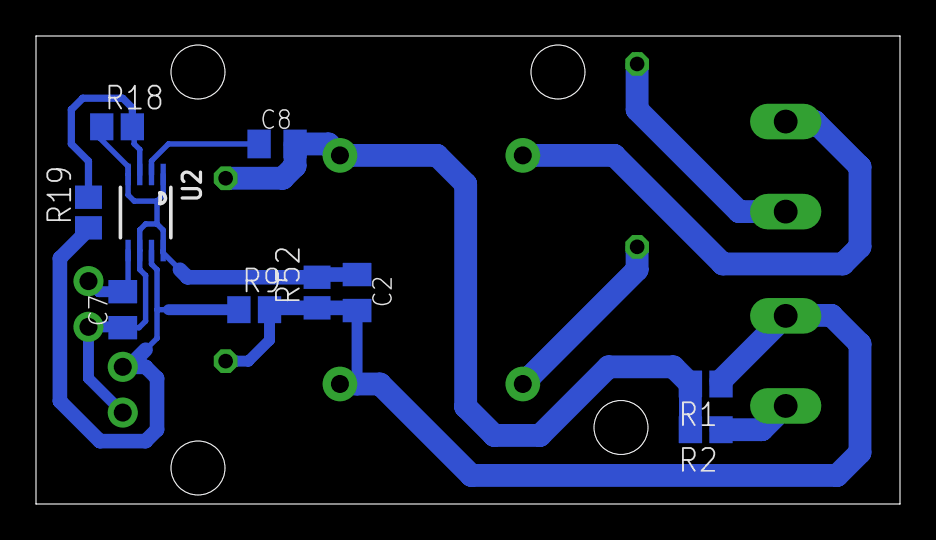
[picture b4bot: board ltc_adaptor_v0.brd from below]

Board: 2 copper layers, 48.0 x 26.0 mm, 17 parts (10 on the bottom side), 11 nets.

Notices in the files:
parts and their libraries:
microbuilder: This work is placed in the public domain, and may be freely used for commercial and non-commercial work with the following conditions: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
SparkFun-Electromechanical: Licensing: Creative Commons ShareAlike 4.0 International - https://creativecommons.org/licenses/by-sa/4.0
